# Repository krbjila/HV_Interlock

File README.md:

# HV_Interlock
Design and code for interlocks for high voltage system

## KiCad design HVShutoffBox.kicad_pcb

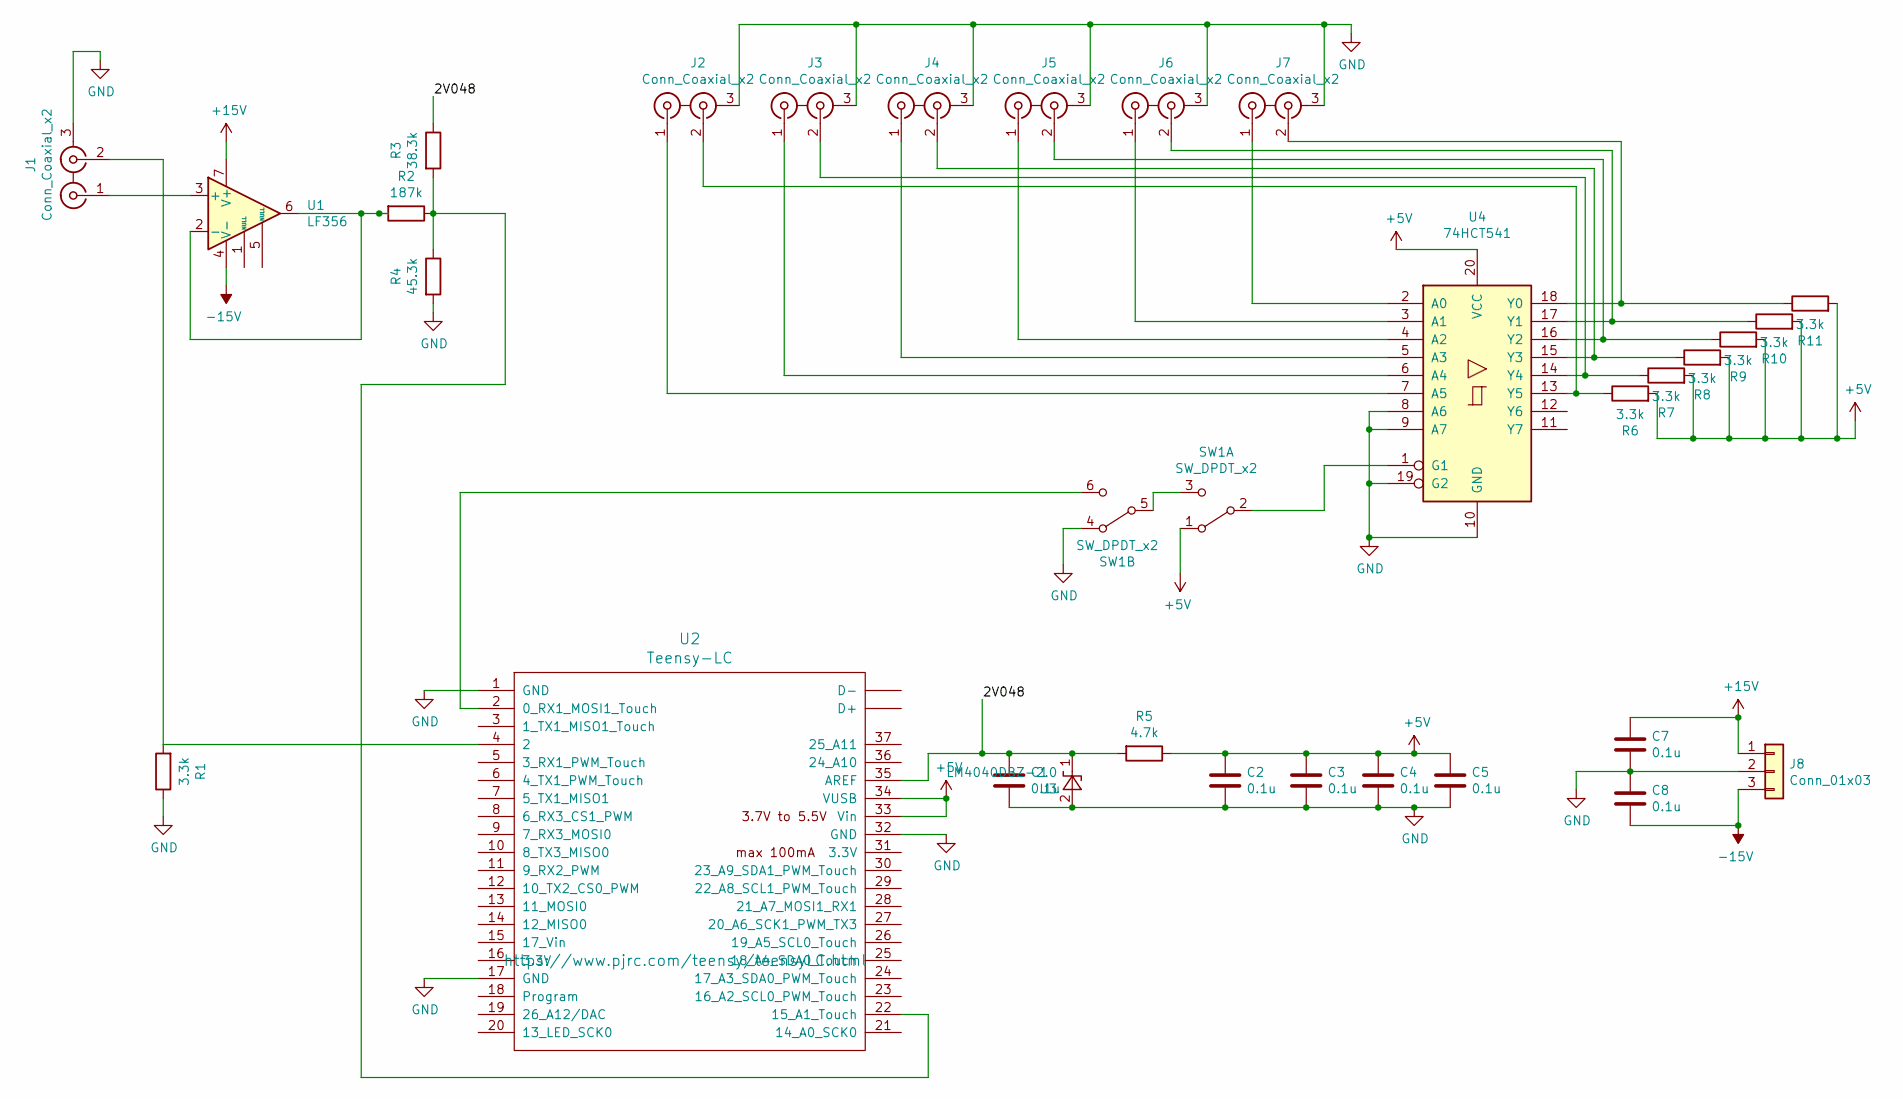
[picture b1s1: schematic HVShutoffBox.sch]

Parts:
C1, C2, C3, C4, C5, C7, C8: 0.1u; C_0603_1608Metric_Pad1.05x0.95mm_HandSolder
J1, J2, J3, J4, J5, J6, J7: Conn_Coaxial_x2; BNC_Amphenol_031-6575_Horizontal
J8: Conn_01x03; Molex_CLIK-Mate_502382-0370_1x03-1MP_P1.25mm_Vertical
R1, R6, R7, R8, R9, R10, R11: 3.3k; R_0603_1608Metric_Pad1.05x0.95mm_HandSolder
R2: 187k; R_0603_1608Metric_Pad1.05x0.95mm_HandSolder
R3: 38.3k; R_0603_1608Metric_Pad1.05x0.95mm_HandSolder
R4: 45.3k; R_0603_1608Metric_Pad1.05x0.95mm_HandSolder
R5: 4.7k; R_0603_1608Metric_Pad1.05x0.95mm_HandSolder
SW1: SW_DPDT_x2; DIP-6_190
U1: LF356; DIP-8_W7.62mm_LongPads
U2: Teensy-LC; Teensy30_31_32_LC
U3: LM4040DBZ-2.0; SOT-23
U4: 74HCT541; TSSOP-20_4.4x6.5mm_P0.65mm

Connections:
+5V: C2.1, C3.1, C4.1, C5.1, R5.1, R6.2, R7.2, R8.2, R9.2, R10.2, R11.2, SW1.1 (A), U2.33 (Vin), U2.34 (VUSB), U4.20 (VCC)
+15V: C7.1, J8.1, U1.7 (V+)
-15V: C8.2, J8.3, U1.4 (V-)
/2V048: C1.1, R3.1, R5.2, U2.35 (AREF), U3.1 (K)
GND: C1.2, C2.2, C3.2, C4.2, C5.2, C7.2, C8.1, J1.3 (EXT), J2.3 (EXT), J3.3 (EXT), J4.3 (EXT), J5.3 (EXT), J6.3 (EXT), J7.3 (EXT), J8.2, R1.1, R4.2, SW1.4 (A), U2.1 (GND), U2.17 (GND), U2.32 (GND), U3.2 (A), U4.8 (A6), U4.9 (A7), U4.10 (GND), U4.19 (G2)
unnamed: J1.1 (IN1), U1.3 (+)
unnamed: J1.2 (IN2), R1.2, U2.4 (2)
unnamed: J2.1 (IN1), U4.7 (A5)
unnamed: J2.2 (IN2), R6.1, U4.13 (Y5)
unnamed: J3.1 (IN1), U4.6 (A4)
unnamed: J3.2 (IN2), R7.1, U4.14 (Y4)
unnamed: J4.1 (IN1), U4.5 (A3)
unnamed: J4.2 (IN2), R8.1, U4.15 (Y3)
unnamed: J5.1 (IN1), U4.4 (A2)
unnamed: J5.2 (IN2), R9.1, U4.16 (Y2)
unnamed: J6.1 (IN1), U4.3 (A1)
unnamed: J6.2 (IN2), R10.1, U4.17 (Y1)
unnamed: J7.1 (IN1), U4.2 (A0)
unnamed: J7.2 (IN2), R11.1, U4.18 (Y0)
unnamed: R2.1, R3.2, R4.1, U2.22 (15_A1_Touch)
unnamed: R2.2, U1.2 (-), U1.6
unnamed: SW1.2 (B), U4.1 (G1)
unnamed: SW1.3 (C), SW1.5 (B)
unnamed: SW1.6 (C), U2.2 (0_RX1_MOSI1_Touch)

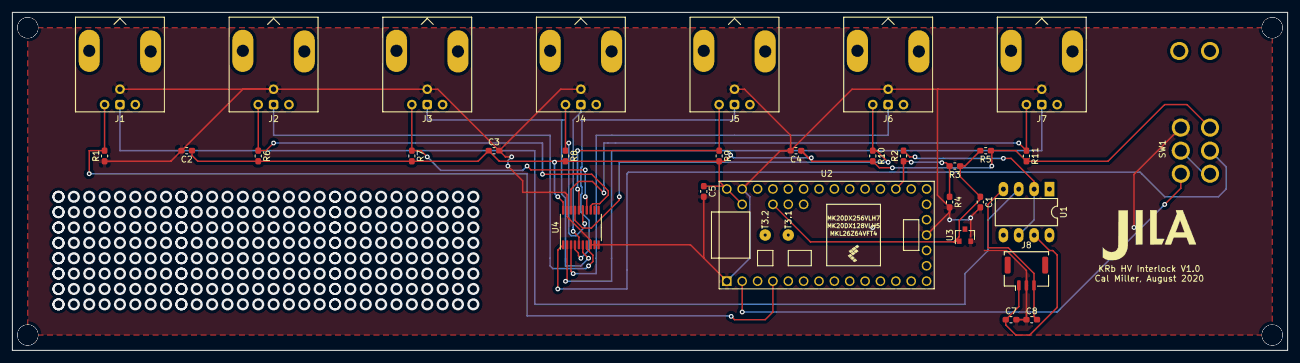
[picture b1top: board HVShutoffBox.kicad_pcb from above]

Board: 2 copper layers, 210.8 x 55.9 mm, 31 parts (0 on the bottom side), 24 nets.

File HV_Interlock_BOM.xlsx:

Id | Designator | Package | Quantity | Designation | Supplier and ref
1 | G*** | JILA_silk | 1 | LOGO
2 | U1 | DIP-8_W7.62mm_LongPads | 1 | LF356
3 | SW1 | DIP-6_190 | 1 | SW_DPDT_x2
4 | U4 | TSSOP-20_4.4x6.5mm_P0.65mm | 1 | 74HCT541
5 | U3 | SOT-23 | 1 | LM4040DBZ-2.0
6 | U2 | Teensy30_31_32_LC | 1 | Teensy-LC
7 | R11,R10,R9,R8,R7,R6,R1 | R_0603_1608Metric_Pad1.05x0.95mm_HandSolder | 7 | 3.3k
8 | R5 | R_0603_1608Metric_Pad1.05x0.95mm_HandSolder | 1 | 4.7 k
9 | R4 | R_0603_1608Metric_Pad1.05x0.95mm_HandSolder | 1 | 45.3k
10 | R3 | R_0603_1608Metric_Pad1.05x0.95mm_HandSolder | 1 | 38.3k
11 | R2 | R_0603_1608Metric_Pad1.05x0.95mm_HandSolder | 1 | 187k
12 | J8 | Molex_CLIK-Mate_502382-0370_1x03-1MP_P1.25mm_Vertical | 1 | Conn_01x03
13 | J7,J6,J5,J4,J3,J2,J1 | BNC_Amphenol_031-6575_Horizontal | 7 | Conn_Coaxial_x2
14 | C8,C7,C5,C4,C3,C2,C1 | C_0603_1608Metric_Pad1.05x0.95mm_HandSolder | 7 | 0.1u

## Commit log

2020-10-06 Uploaded design files and first generation code
2023-08-24 minor fixes to microcontroller code
